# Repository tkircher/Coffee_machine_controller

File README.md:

# Coffee_machine_controller
This is a control board for a Linea Mini coffee machine

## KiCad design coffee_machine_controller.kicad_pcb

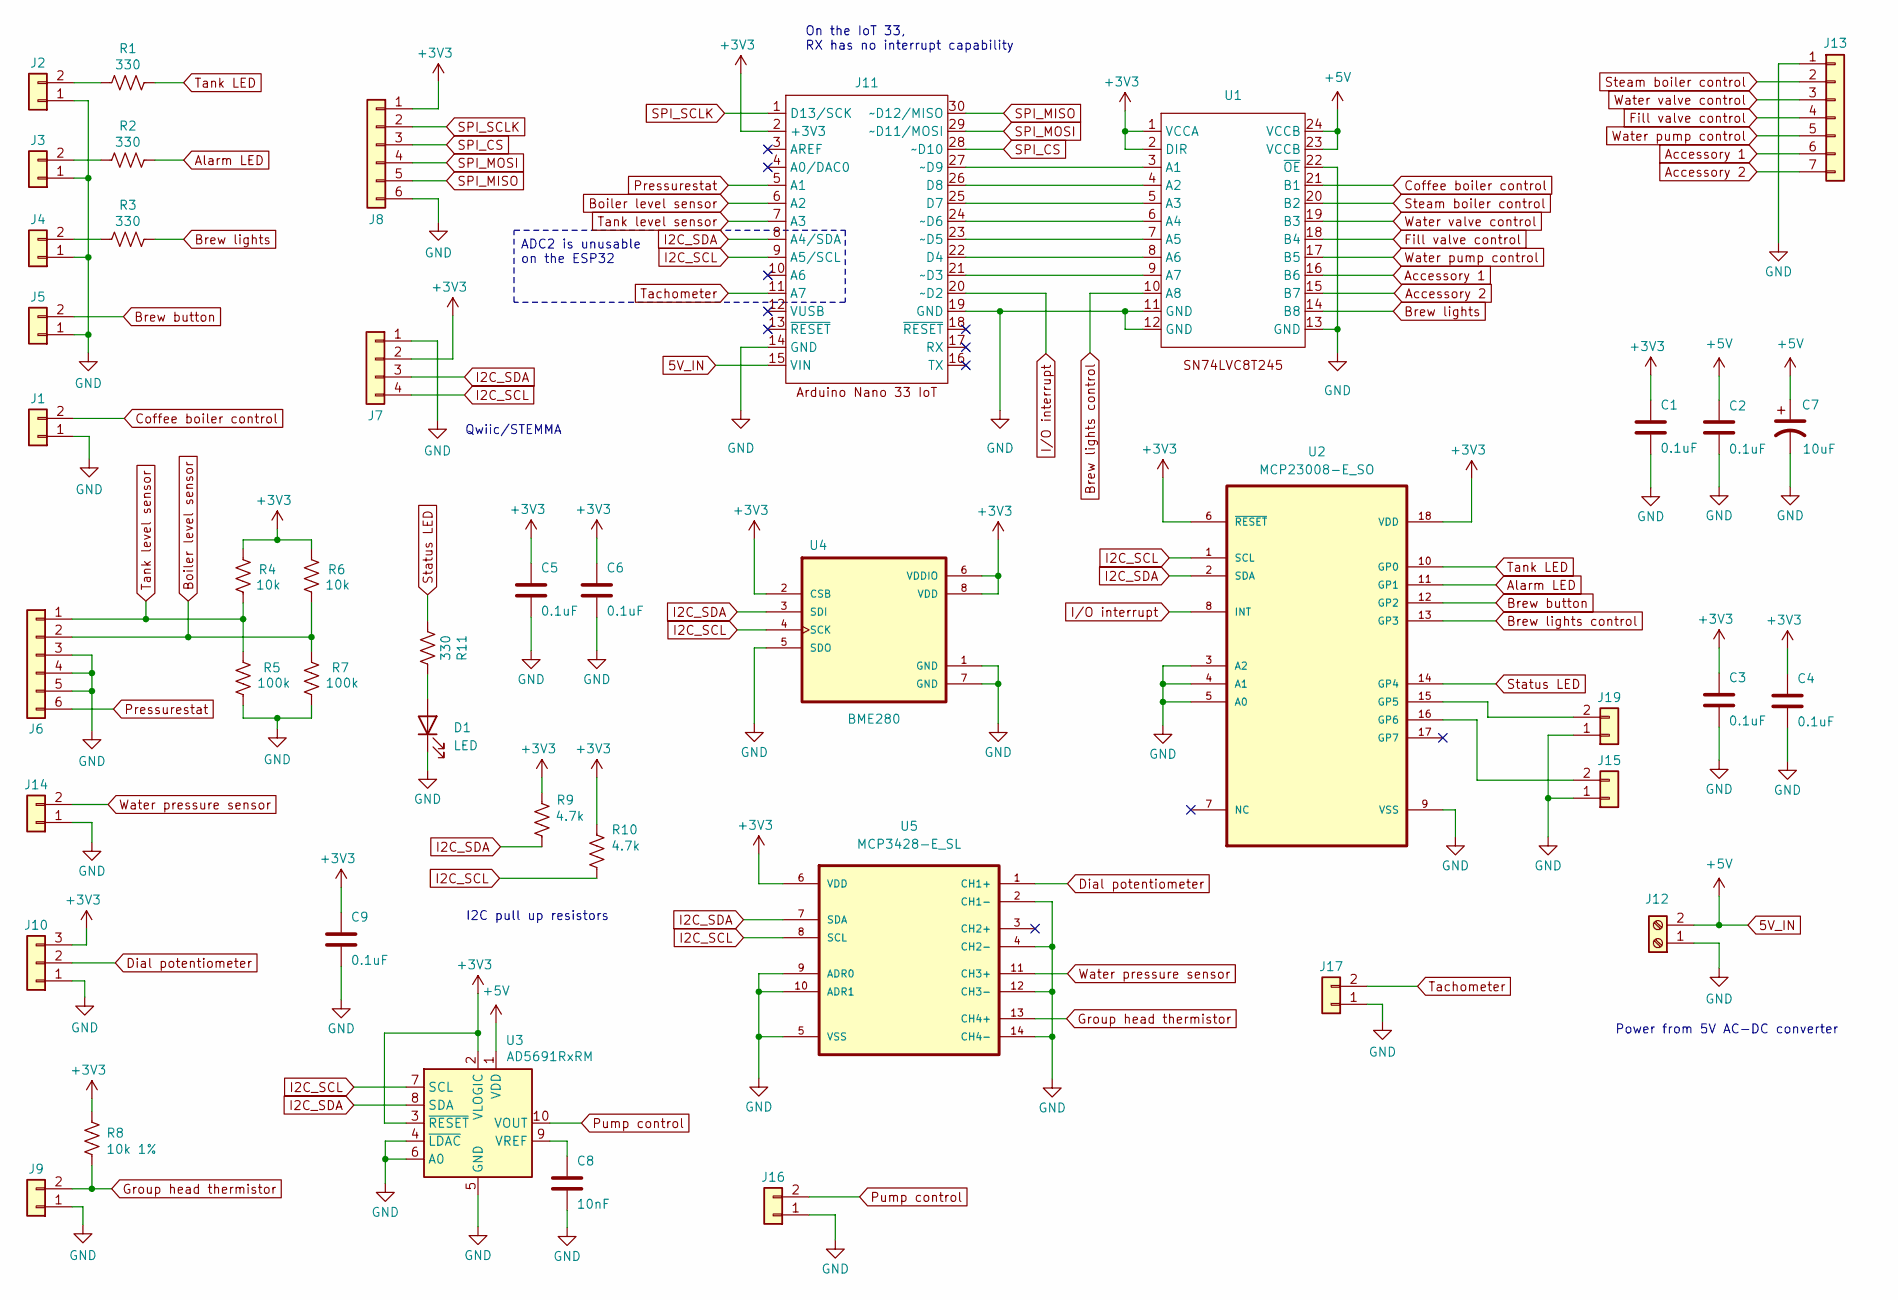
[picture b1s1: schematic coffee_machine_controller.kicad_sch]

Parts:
C1, C2, C3, C4, C5, C6, C9: 0.1uF; C_0805_2012Metric
C7: 10uF; CP_EIA-3216-18_Kemet-A
C8: 10nF; C_0805_2012Metric
D1: LED; LED_0805_2012Metric
J1, J2, J3, J4, J5, J9, J14, J15, J16, J17, J19: Conn_01x02; PinHeader_1x02_P2.54mm_Vertical
J6: Conn_01x06; PinHeader_1x06_P2.54mm_Vertical
J7: Conn_01x04; JST_SH_SM04B-SRSS-TB_1x04-1MP_P1.00mm_Horizontal
J8: Conn_01x06; PinHeader_1x06_P2.54mm_Vertical_DNP
J10: Conn_01x03; PinHeader_1x03_P2.54mm_Vertical
J11: Arduino_Nano_33_IoT_SMD
J12: Screw_Terminal_01x02; Terminal_block_01x02
J13: Conn_01x07; PinSocket_1x07_P2.54mm_Vertical
R1, R2, R3, R11: 330; R_0805_2012Metric
R4, R6: 10k; R_0805_2012Metric
R5, R7: 100k; R_0805_2012Metric
R8: 10k 1%; R_0805_2012Metric
R9, R10: 4.7k; R_0805_2012Metric
U1: SOP127P780X200-24N
U2: MCP23008-E_SO; SOIC127P1030X265-18N
U3: AD5691RxRM; MSOP-10_3x3mm_P0.5mm
U4: BME280; PSON65P250X250X100-8N
U5: MCP3428-E_SL; SOIC127P600X175-14N

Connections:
5V_IN: C2.1, C7.1, J11.15 (VIN), J12.2, U1.23 (VCCB), U1.24 (VCCB), U3.1 (VDD)
+3V3: C1.1, C3.1, C4.1, C5.1, C6.1, C9.1, J7.2, J8.1, J10.3, J11.2 (+3V3), R4.2, R6.2, R8.2, R9.2, R10.2, U1.1 (VCCA), U1.2 (DIR), U2.6 (~RESET), U2.18 (VDD), U3.2 (VLOGIC), U3.3 (~RESET), U4.2 (CSB), U4.6 (VDDIO), U4.8 (VDD), U5.6 (VDD)
Accessory 1: J13.6, U1.16 (B6)
Accessory 2: J13.7, U1.15 (B7)
Alarm LED: R2.2, U2.11 (GP1)
Boiler level sensor: J6.2, J11.6 (A2), R6.1, R7.2
Brew button: J5.2, U2.12 (GP2)
Brew lights: R3.2, U1.14 (B8)
Brew lights control: U1.10 (A8), U2.13 (GP3)
Coffee boiler control: J1.2, U1.21 (B1)
Dial potentiometer: J10.2, U5.1 (CH1+)
Fill valve control: J13.4, U1.18 (B4)
GND: C1.2, C2.2, C3.2, C4.2, C5.2, C6.2, C7.2, C8.2, C9.2, D1.1 (K), J1.1, J2.1, J3.1, J4.1, J5.1, J6.3, J6.4, J6.5, J7.1, J8.6, J9.1, J10.1, J11.14 (GND), J11.19 (GND), J12.1, J13.1, J14.1, J15.1, J16.1, J17.1, J19.1, R5.1, R7.1, U1.11 (GND), U1.12 (GND), U1.13 (GND), U1.22 (~OE), U2.3 (A2), U2.4 (A1), U2.5 (A0), U2.9 (VSS), U3.4 (~LDAC), U3.5 (GND), U3.6 (A0), U4.1 (GND), U4.5 (SDO), U4.7 (GND), U5.2 (CH1-), U5.4 (CH2-), U5.5 (VSS), U5.9 (ADR0), U5.10 (ADR1), U5.12 (CH3-), U5.14 (CH4-)
Group head thermistor: J9.2, R8.1, U5.13 (CH4+)
I2C_SCL: J7.4, J11.9 (A5/SCL), R10.1, U2.1 (SCL), U3.7 (SCL), U4.4 (SCK), U5.8 (SCL)
I2C_SDA: J7.3, J11.8 (A4/SDA), R9.1, U2.2 (SDA), U3.8 (SDA), U4.3 (SDI), U5.7 (SDA)
I/O interrupt: J11.20 (~D2), U2.8 (INT)
unnamed: D1.2 (A), R11.2
unnamed: J2.2, R1.1
unnamed: J3.2, R2.1
unnamed: J4.2, R3.1
unnamed: J11.22 (D4), U1.8 (A6)
unnamed: J11.25 (D7), U1.5 (A3)
unnamed: J11.26 (D8), U1.4 (A2)
unnamed: J11.21 (~D3), U1.9 (A7)
unnamed: J11.23 (~D5), U1.7 (A5)
unnamed: J11.24 (~D6), U1.6 (A4)
unnamed: J11.27 (~D9), U1.3 (A1)
unnamed: J15.2, U2.16 (GP6)
unnamed: J19.2, U2.15 (GP5)
unnamed: C8.1, U3.9 (VREF)
Pressurestat: J6.6, J11.5 (A1)
Pump control: J16.2, U3.10 (VOUT)
SPI_CS: J8.3, J11.28 (~D10)
SPI_MISO: J8.5, J11.30 (~D12/MISO)
SPI_MOSI: J8.4, J11.29 (~D11/MOSI)
SPI_SCLK: J8.2, J11.1 (D13/SCK)
Status LED: R11.1, U2.14 (GP4)
Steam boiler control: J13.2, U1.20 (B2)
Tachometer: J11.11 (A7), J17.2
Tank LED: R1.2, U2.10 (GP0)
Tank level sensor: J6.1, J11.7 (A3), R4.1, R5.2
Water pressure sensor: J14.2, U5.11 (CH3+)
Water pump control: J13.5, U1.17 (B5)
Water valve control: J13.3, U1.19 (B3)

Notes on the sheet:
Qwiic/STEMMA
I2C pull up resistors
On the IoT 33, RX has no interrupt capability
Power from 5V AC-DC converter
ADC2 is unusable on the ESP32

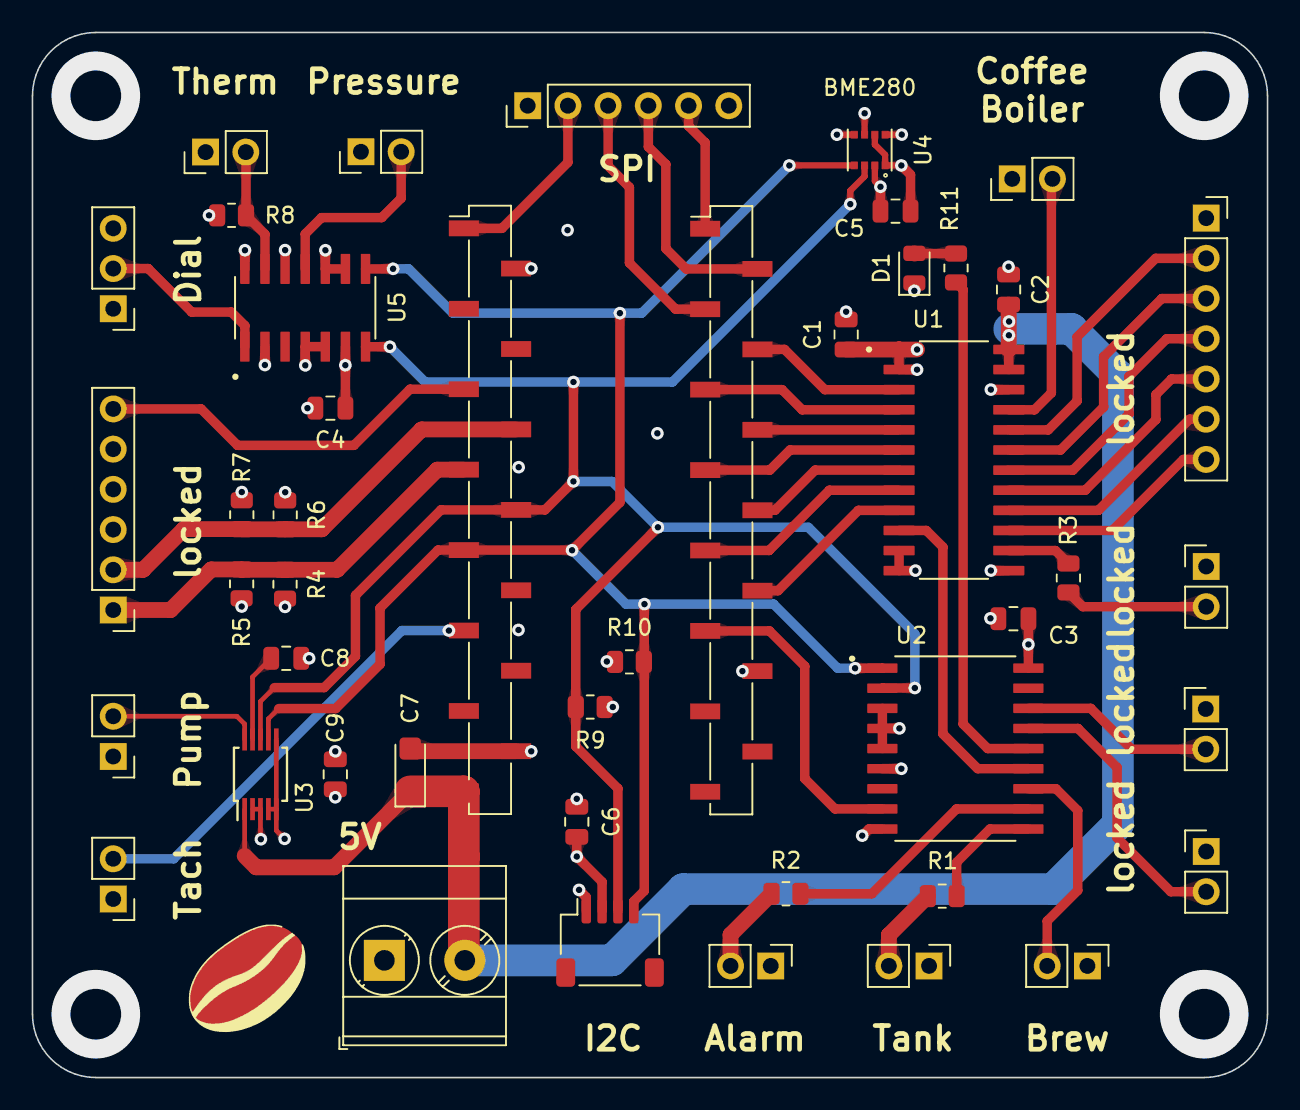
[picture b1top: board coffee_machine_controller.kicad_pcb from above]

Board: 4 copper layers, 78.0 x 66.0 mm, 44 parts (0 on the bottom side), 45 nets.

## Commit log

2025-01-06 Added a KiCAD board render
2025-01-06 Added photo of real board
